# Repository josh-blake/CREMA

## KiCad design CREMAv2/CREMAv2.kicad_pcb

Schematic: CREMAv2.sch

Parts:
C1: 0.1uF; C_1206_3216Metric; Digikey Part Number 478-3797-1-ND
C2: 330nF; C_1206_3216Metric; Digikey Part Number 478-6055-1-ND
C3: 4.7uF; C_1206_3216Metric; Digikey Part Number 399-C1206X475J5RAC7800CT-ND
IC1: ADS124S06IPBSR; TQFP-32_7x7mm_P0.8mm; Manufacturer_Part_Number ADS124S06IPBSR; Mouser Part Number 595-ADS124S06IPBSR
J1: SPI; PinHeader_2x03_P1.00mm_Vertical_SMD; Digikey Part Number WM17457-ND
J2: RTD1; PinHeader_1x02_P1.00mm_Vertical_SMD_Pin1Left; Digikey Part Number WM9852-ND
J3: RTD2; PinHeader_1x02_P1.00mm_Vertical_SMD_Pin1Left; Digikey Part Number WM9852-ND
R1, R2: 100R; R_0603_1608Metric; Digikey Part Number RMCF0603FT100RCT-ND
R3, R4: 130R; R_0603_1608Metric; Digikey Part Number 408-1679-1-ND
R5, R6: 22K; R_0603_1608Metric; Digikey Part Number RMCF0603FG22K0CT-ND
R7, R11: 750R; R_0603_1608Metric; Digikey Part Number RG16N750WCT-ND
R8, R9, R10, R12: 47R; R_0603_1608Metric; Digikey Part Number RMCF0603FT47R0CT-ND

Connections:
+3V3: C1.1, C2.1, IC1.15 (IOVDD), IC1.16 (DVDD), IC1.18 (~RESET), IC1.26 (AVDD), J1.2, R5.2, R6.2
EXTI_A2DRDY: IC1.13 (~DRDY), R6.1
GND: C1.2, C2.2, C3.1, IC1.8 (START/SYNC), IC1.14 (DGND), IC1.17 (CLK), IC1.24 (REFCOM), IC1.27 (AVSS), IC1.28 (AVSS-SW), J1.6, R1.1, R2.1
unnamed: C3.2, IC1.23 (REFOUT)
unnamed: IC1.2 (AIN5), R3.1
unnamed: IC1.6 (AIN1), R4.1
unnamed: IC1.9 (~CS), R5.1, R8.1
unnamed: IC1.10 (DIN), R9.1
unnamed: IC1.11 (SCLK), R10.1
unnamed: IC1.12 (DOUT/~DRDY), R12.1
unnamed: IC1.5 (AIN2), IC1.30 (REFP0), R11.2
unnamed: IC1.4 (AIN3), IC1.32 (REFP1/AIN6), R7.2
RTD1N: J2.2, R1.2, R4.2
RTD1P: IC1.7 (AIN0), IC1.29 (REFN0), J2.1, R11.1
RTD2N: J3.2, R2.2, R3.2
RTD2P: IC1.3 (AIN4), IC1.31 (REFN1/AIN7), J3.1, R7.1
SPI_CLK: J1.3, R10.2
SPI_CS: J1.5, R8.2
SPI_MISO: J1.1, R12.2
SPI_MOSI: J1.4, R9.2

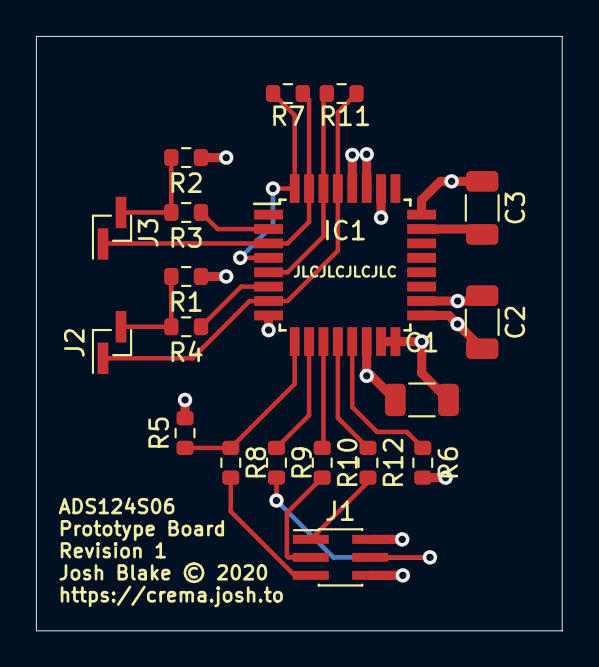
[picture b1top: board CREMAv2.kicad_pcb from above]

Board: 4 copper layers, 29.2 x 33.0 mm, 19 parts (0 on the bottom side), 20 nets.

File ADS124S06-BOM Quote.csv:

Reference, Value, Description, Digikey Part Number, Digikey Price
C1,0.1uF,CAP CER 0.1UF 50V X7R 1206,478-3797-1-ND,0.44
C2,330nF,CAP CER 0.33UF 50V X7R 1206,478-6055-1-ND,0.68
IC1,ADS124S06IPBSR,"24-Bit, 4kSPS, 6-Ch Delta-Sigma ADC with PGA and Voltage Reference for Precision Sensor Measurement",296-45169-1-ND,13.57
C3,4.7uF,CAP CER 4.70UF 50.0V 1206,399-C1206X475J5RAC7800CT-ND,0.99
R11,750R,RES SMD 750 OHM 0.05% 1/10W 0603,RG16N750WCT-ND,1.16
R4,130R,RES SMD 130 OHM 0.05% 1/10W 0603,408-1679-1-ND,1.16
R1,100R,RES 100 OHM 1% 1/10W 0603,RMCF0603FT100RCT-ND,0.15
R7,750R,RES SMD 750 OHM 0.05% 1/10W 0603,RG16N750WCT-ND,1.16
R2,100R,RES 100 OHM 1% 1/10W 0603,RMCF0603FT100RCT-ND,0.15
R3,130R,RES SMD 130 OHM 0.05% 1/10W 0603,408-1679-1-ND,1.16
R12,47R,RES 47 OHM 1% 1/10W 0603,RMCF0603FT47R0CT-ND,0.15
R10,47R,RES 47 OHM 1% 1/10W 0603,RMCF0603FT47R0CT-ND,0.15
R9,47R,RES 47 OHM 1% 1/10W 0603,RMCF0603FT47R0CT-ND,0.15
R5,22K,RES 22K OHM 1% 1/10W 0603,RMCF0603FG22K0CT-ND,0.15
R6,22K,RES 22K OHM 1% 1/10W 0603,RMCF0603FG22K0CT-ND,0.15
R8,47R,RES 47 OHM 1% 1/10W 0603,RMCF0603FT47R0CT-ND,0.15
J2,RTD1,CONN HEADER SMD 2POS 2.54MM,WM9852-ND,0.8
J3,RTD2,CONN HEADER SMD 2POS 2.54MM,WM9852-ND,0.8
J1,SPI,CONN HEADER SMD 6POS 2.54MM,WM17457-ND,0.86
,,,,
,,,,23.98

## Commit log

2020-11-25 Initial commit. New ADC - TI ADS124S06 prototype board.
2020-11-25 Updated with some extra PDFs.
2020-11-25 Updated directory structure.
2020-11-28 Added power to the schematic. Updated PDFs. Added KiCad symbols.

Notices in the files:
CREMAv2/CREMAv2.kicad_pcb:
Josh Blake © 2020
